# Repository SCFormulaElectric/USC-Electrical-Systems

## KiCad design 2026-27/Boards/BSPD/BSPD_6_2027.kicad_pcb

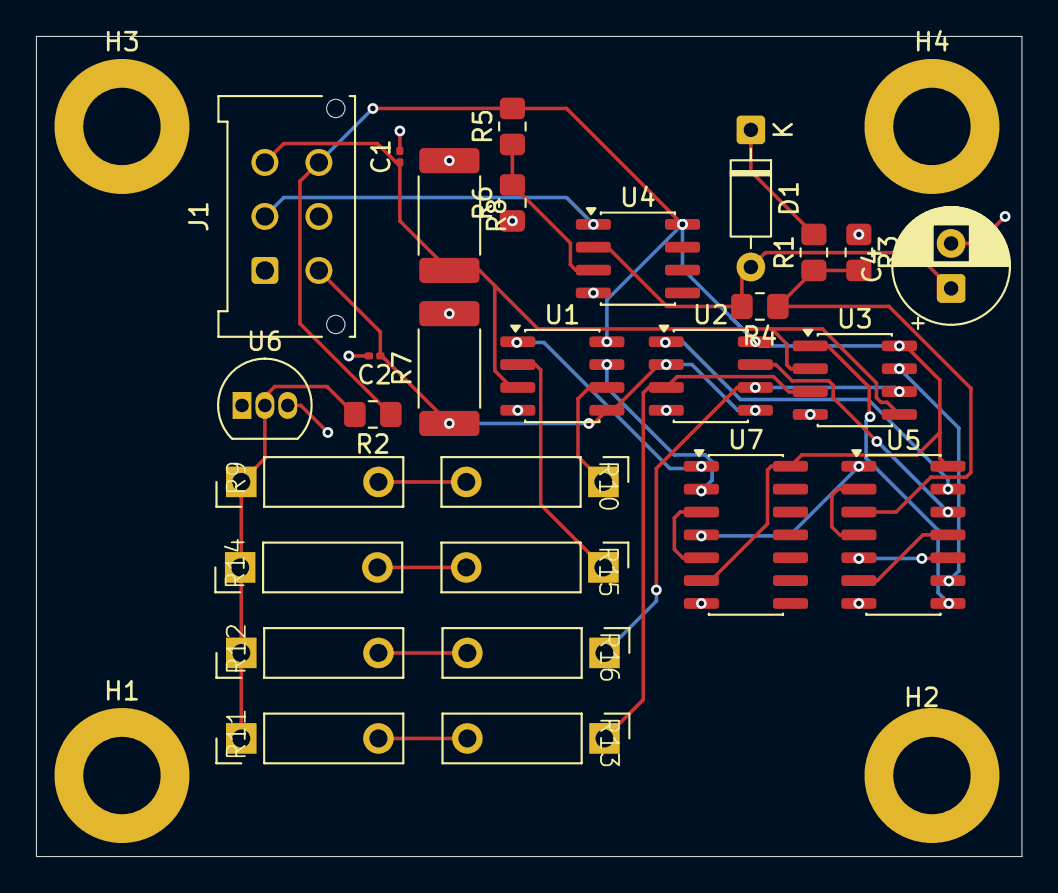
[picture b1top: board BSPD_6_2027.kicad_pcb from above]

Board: 2 copper layers, 54.8 x 45.6 mm, 32 parts (0 on the bottom side), 25 nets.

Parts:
C1, C2: 0.1u; C_0201_0603Metric
C4: 12u; CP_Radial_D6.3mm_P2.50mm
D1: 1N4148; D_DO-35_SOD27_P7.62mm_Horizontal
H1, H2, H3, H4: MountingHole_Pad; MountingHole_4.3mm_M4_DIN965_Pad
J1: 043045-0612; Molex_Micro-Fit_3.0_43045-0612_2x03_P3.00mm_Vertical
R1: 1k; R_0805_2012Metric_Pad1.20x1.40mm_HandSolder
R2: 2.7k; R_0805_2012Metric_Pad1.20x1.40mm_HandSolder
R3: 5k; R_0805_2012Metric_Pad1.20x1.40mm_HandSolder
R4: 50k; R_0805_2012Metric_Pad1.20x1.40mm_HandSolder
R5, R6: 47k; R_0805_2012Metric_Pad1.20x1.40mm_HandSolder
R7, R8: 10k; R_2512_6332Metric_Pad1.40x3.35mm_HandSolder
R9, R11: 1k; SMD TH Adapter
R10, R13: 18k; SMD TH Adapter
R12: 2k; SMD TH Adapter
R14: 1.2k; SMD TH Adapter
R15: 1.3k; SMD TH Adapter
R16: 100; SMD TH Adapter
U1, U2, U3, U4: LM358; SOIC-8_3.9x4.9mm_P1.27mm
U5: HEF4071B (OR); SOIC-14_3.9x8.7mm_P1.27mm
U6: LM4040LP-5; TO-92_Inline
U7: HEF4011B (NAND); SOIC-14_3.9x8.7mm_P1.27mm

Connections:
0.25V: R13.1, U2.3 (+), U3.3 (+)
4.7V: R16.1, U2.6 (-), U3.6 (-)
5V: R2.2, R9.1, R11.1, R12.1, R14.1, U6.2 (K)
12V: J1.6, R2.1, R5.2, U1.8 (V+), U2.8 (V+), U3.8 (V+), U4.8 (V+), U5.14 (VDD), U7.6 (2B), U7.14 (VDD)
BSPD_signal: J1.2, U4.1
GND: C1.2, C2.2, C4.2, H1.1 (1_1), H2.1 (1_1), H3.1 (1_1), H4.1 (1_1), J1.5, R3.1, R6.1, R7.2, R8.1, U1.4 (V-), U2.4 (V-), U3.4 (V-), U4.4 (V-), U5.7 (VSS), U6.3 (A), U7.7 (VSS)
unnamed: C4.1, D1.2 (A), R4.2, U4.2 (-)
unnamed: D1.1 (K), R1.2
unnamed: R15.1, U1.2 (-)
unnamed: R10.1, U1.6 (-)
unnamed: R5.1, R6.2, U4.3 (+)
unnamed: U5.2 (1B), U5.4 (2Y)
unnamed: U5.5 (2A), U5.10 (3Y)
unnamed: U5.6 (2B), U5.11 (4Y)
unnamed: U7.3 (1Y), U7.5 (2A)
brake: C2.1, J1.4, R7.1, U1.5 (+), U2.2 (-), U2.5 (+)
brake_short_ground: U2.1, U5.13 (4B)
brake_short_power: U2.7, U5.12 (4A)
current: C1.1, J1.3, R8.2, U1.3 (+), U3.2 (-), U3.5 (+)
current_short_ground: U3.1, U5.8 (3A)
current_short_power: U3.7, U5.9 (3B)
fault: R1.1, R3.2, R4.1, U5.3 (1Y)
fault_1: U5.1 (1A), U7.4 (2Y)
hard_brake: U1.7, U7.2 (1B)
high_current: U1.1, U7.1 (1A)

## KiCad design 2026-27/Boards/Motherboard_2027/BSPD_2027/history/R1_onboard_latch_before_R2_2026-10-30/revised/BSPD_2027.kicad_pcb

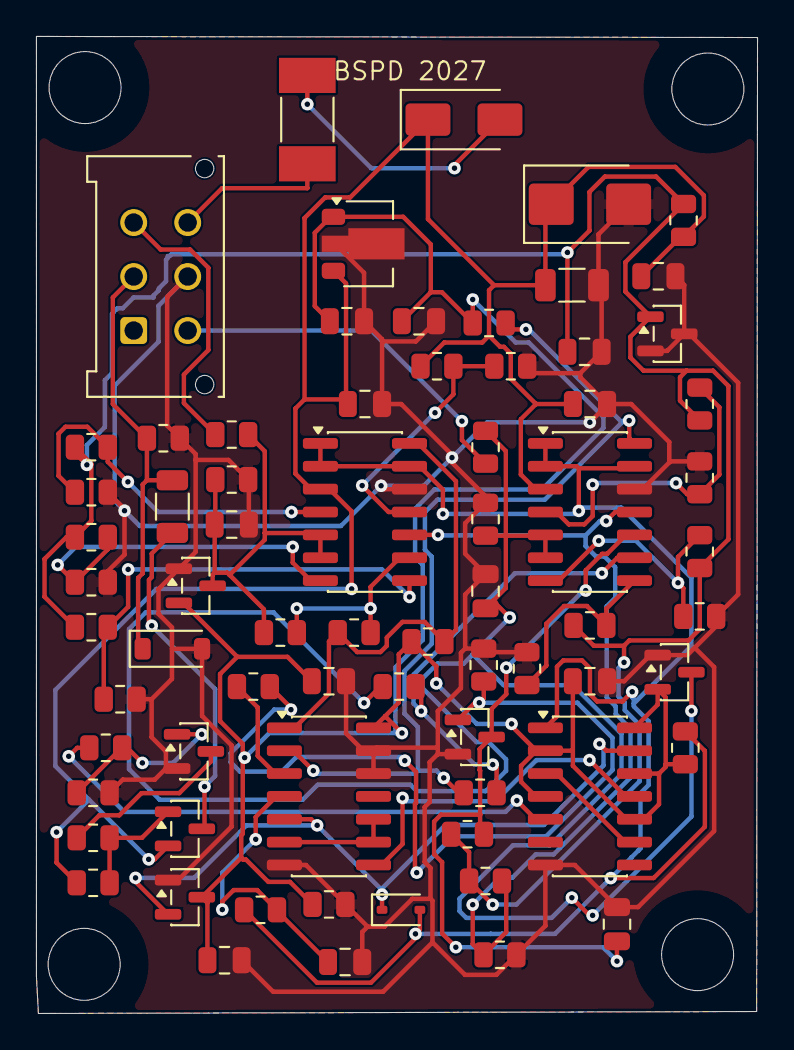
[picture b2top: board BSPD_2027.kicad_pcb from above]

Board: 2 copper layers, 40.1 x 54.3 mm, 71 parts (0 on the bottom side), 37 nets.

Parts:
C1: 10uF/50V; C_1206_3216Metric
C2, C4, C5, C6, C7, C9, C11, C13, C14: 100nF/50V; C_0805_2012Metric
C3: 1uF/50V; C_0805_2012Metric
C8, C10: 10nF/50V; C_0805_2012Metric
C12: 10uF/25V X7R 10%; C_0805_2012Metric
D1: SS14; D_SMA
D2: SMBJ18A; D_SMB
D3: BAT54WS-7-F; D_SOD-323
D4: BZT52C15-7-F; D_SOD-123
F1: 0451.250MRL; Fuse_Littelfuse-NANO2-451_453
J1: 043045-0612; Molex_Micro-Fit_3.0_43045-0612_2x03_P3.00mm_Vertical
Q1: 2N7002,215; SOT-23
Q2: MMBT3904,215; SOT-23
Q3: MMBT3906,215; SOT-23
R1, R11: 1k 1%; R_0805_2012Metric
R2: 3.3k 1%; R_0805_2012Metric
R3, R4, R6, R7, R10, R15, R16, R17, R23: 10k 0.1%; R_0805_2012Metric
R5: 1M 1%; R_0805_2012Metric
R8: 9.53k 0.1%; R_0805_2012Metric
R9: 28k 0.1%; R_0805_2012Metric
R12: 4.7M 1%; R_0805_2012Metric
R13, R19, R21, R24, R26, R32, R34: 10k 1%; R_0805_2012Metric
R14: 33k 1%; R_0805_2012Metric
R18: 115k 1%; R_0805_2012Metric
R20: 8.66k 1%; R_0805_2012Metric
R22: 40.2k 0.1%; R_0805_2012Metric
R25: 2.2M 1%; R_0805_2012Metric
R27: 39k 1%; R_0805_2012Metric
R28, R29: 47k 0.1%; R_0805_2012Metric
R30: 470 1%; R_0805_2012Metric
R31, R35, R37: 100k 1%; R_0805_2012Metric
R33, R36, R39: 47k 1%; R_0805_2012Metric
R38: 2.2k 1%; R_1206_3216Metric
U1: L78L05ABUTR; SOT-89-3
U2: LM4040AIM3-5.0/NOPB; SOT-23
U3: MCP809T-450I/TT; SOT-23
U4, U6: LM2901BIDR; SOIC-14_3.9x8.7mm_P1.27mm
U5, U7: BAT54S,215; SOT-23
U8: 74HC132D,653; SOIC-14_3.9x8.7mm_P1.27mm
U9: 74HC74D,653; SOIC-14_3.9x8.7mm_P1.27mm

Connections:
ARM_CLK: U9.3 (CLK1), U9.9 (Q2)
BOOT_CLK: U8.8 (3Y), U9.11 (CLK2)
BSPD_SIGNAL: D4.1 (K), J1.2, R38.2, R39.1
B_CMP: R24.2, R25.2, U6.9 (IN3+)
B_HARD: R25.1, R26.2, U6.14 (OUT3), U8.2 (1B)
B_HIGH: R20.2, R21.1, U6.7 (IN2+)
B_LOW: R18.2, R19.1, U6.4 (IN1-)
B_RAW: J1.4, R16.1
B_SENSE: C10.1, R16.2, R17.1, R24.1, U6.5 (IN1+), U6.6 (IN2-), U7.3 (K1/A2)
B_THRESH: R22.2, R23.1, U6.8 (IN3-)
CLK_INV: U8.6 (2Y), U8.9 (3A), U8.10 (3B)
C_HIGH: R12.1, R13.2, U4.14 (OUT3), U8.1 (1A)
DISCHARGE: R30.1, U8.3 (1Y)
DIS_GATE: Q1.1 (G), R30.2, R31.1
FAULT_OK: D3.2 (A), R32.2, R33.1, U4.1 (OUT1), U4.2 (OUT2), U4.13 (OUT4), U6.1 (OUT1), U6.2 (OUT2), U6.13 (OUT4), U9.1 (CLR1_N)
GND: C1.2, C2.2, C3.2, C4.2, C5.2, C6.2, C7.2, C8.2, C9.2, C10.2, C11.2, C12.2, C13.2, C14.2, D2.2 (A), D4.2 (A), J1.5, Q1.2 (S), Q2.2 (E), R1.2, R4.2, R6.2, R8.2, R10.2, R15.2, R17.2, R19.2, R21.2, R23.2, R29.2, R31.2, R35.2, R39.2, U1.2 (GND), U2.2 (A), U2.3 (A/NC), U3.1 (GND), U4.12 (GND), U5.1 (A1), U6.12 (GND), U7.1 (A1), U8.7 (GND), U8.12 (4A), U8.13 (4B), U9.7 (GND)
I_CMP: R11.2, R12.2, U4.9 (IN3+)
I_HIGH: R7.2, R8.1, U4.7 (IN2+)
I_LOW: R5.2, R6.1, U4.4 (IN1-)
I_RAW: J1.3, R3.1
I_SENSE: C8.1, R3.2, R4.1, R11.1, U4.5 (IN1+), U4.6 (IN2-), U5.3 (K1/A2)
I_THRESH: R9.2, R10.1, U4.8 (IN3-)
N_BASE: Q2.1 (B), R34.2, R35.1
N_COL: Q2.3 (C), R36.1
OUT_SRC: Q3.3 (C), R38.1
PERMIT: R34.1, U9.5 (Q1)
POR_N: D3.1 (K), U3.2 (RESET_N), U8.5 (2B), U9.13 (CLR2_N)
P_BASE: Q3.1 (B), R36.2, R37.2
REF5: C5.1, R2.2, R5.1, R7.1, R9.1, R18.1, R20.1, R22.1, R27.1, R28.1, U2.1 (K)
REF_HALF: R28.2, R29.1, U4.10 (IN4-), U6.11 (IN4+)
START_RC: C14.1, R33.2, U8.4 (2A)
TIMER: C12.1, Q1.3 (D), R27.2, U6.10 (IN4-)
V5: C3.1, C4.1, C6.1, C11.1, C13.1, R1.1, R13.1, R26.1, R32.1, U1.1 (OUT), U3.3 (VDD), U5.2 (K2), U7.2 (K2), U8.14 (VCC), U9.2 (D1), U9.4 (PRE1_N), U9.10 (PRE2_N), U9.12 (D2), U9.14 (VCC)
VIN: F1.1, J1.6
VIN_DIV: R14.2, R15.1, U4.11 (IN4+)
VIN_F: D1.2 (A), F1.2
VP: C1.1, C2.1, C7.1, C9.1, D1.1 (K), D2.1 (K), Q3.2 (E), R2.1, R14.1, R37.1, U1.3 (IN), U4.3 (VCC), U6.3 (VCC)

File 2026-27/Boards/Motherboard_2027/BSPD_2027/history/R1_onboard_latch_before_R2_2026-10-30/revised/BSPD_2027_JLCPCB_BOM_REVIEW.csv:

Comment,Designator,Footprint,LCSC Part #
043045-0612,J1,Molex_Micro-Fit_3.0_43045-0612_2x03_P3.00mm_Vertical,C234188
0451.250MRL,F1,Fuse_Littelfuse-NANO2-451_453,C151116
SS14,D1,D_SMA,C2480
SMBJ18A,D2,D_SMB,C151256
10uF/50V,C1,C_1206_3216Metric,C77092
100nF/50V,"C2,C4,C5,C6,C7,C9,C11,C13,C14",C_0805_2012Metric,C1711
L78L05ABUTR,U1,SOT-89-3,C42738
1uF/50V,C3,C_0805_2012Metric,C28323
1k 1%,"R1,R11",R_0805_2012Metric,C17513
3.3k 1%,R2,R_0805_2012Metric,C26010
LM4040AIM3-5.0/NOPB,U2,SOT-23,C140239
MCP809T-450I/TT,U3,SOT-23,C511285
LM2901BIDR,"U4,U6",SOIC-14_3.9x8.7mm_P1.27mm,C22427890
10k 0.1%,"R3,R4,R6,R7,R10,R15,R16,R17,R23",R_0805_2012Metric,C110775
10nF/50V,"C8,C10",C_0805_2012Metric,C282728
"BAT54S,215","U5,U7",SOT-23,C47546
1M 1%,R5,R_0805_2012Metric,C17514
9.53k 0.1%,R8,R_0805_2012Metric,C865722
28k 0.1%,R9,R_0805_2012Metric,C865356
4.7M 1%,R12,R_0805_2012Metric,C17674
10k 1%,"R13,R19,R21,R24,R26,R32,R34",R_0805_2012Metric,C17414
33k 1%,R14,R_0805_2012Metric,C17633
115k 1%,R18,R_0805_2012Metric,C407430
8.66k 1%,R20,R_0805_2012Metric,C17832
40.2k 0.1%,R22,R_0805_2012Metric,C865475
2.2M 1%,R25,R_0805_2012Metric,C137552
"74HC132D,653",U8,SOIC-14_3.9x8.7mm_P1.27mm,C5601
39k 1%,R27,R_0805_2012Metric,C25826
10uF/25V X7R 10%,C12,C_0805_2012Metric,C237493
47k 0.1%,"R28,R29",R_0805_2012Metric,C865515
470 1%,R30,R_0805_2012Metric,C17710
100k 1%,"R31,R35,R37",R_0805_2012Metric,C149504
"2N7002,215",Q1,SOT-23,C65189
"74HC74D,653",U9,SOIC-14_3.9x8.7mm_P1.27mm,C27597
BAT54WS-7-F,D3,D_SOD-323,C124205
47k 1%,"R33,R36,R39",R_0805_2012Metric,C17713
"MMBT3904,215",Q2,SOT-23,C426835
"MMBT3906,215",Q3,SOT-23,C75549
2.2k 1%,R38,R_1206_3216Metric,C17948
BZT52C15-7-F,D4,D_SOD-123,C177014

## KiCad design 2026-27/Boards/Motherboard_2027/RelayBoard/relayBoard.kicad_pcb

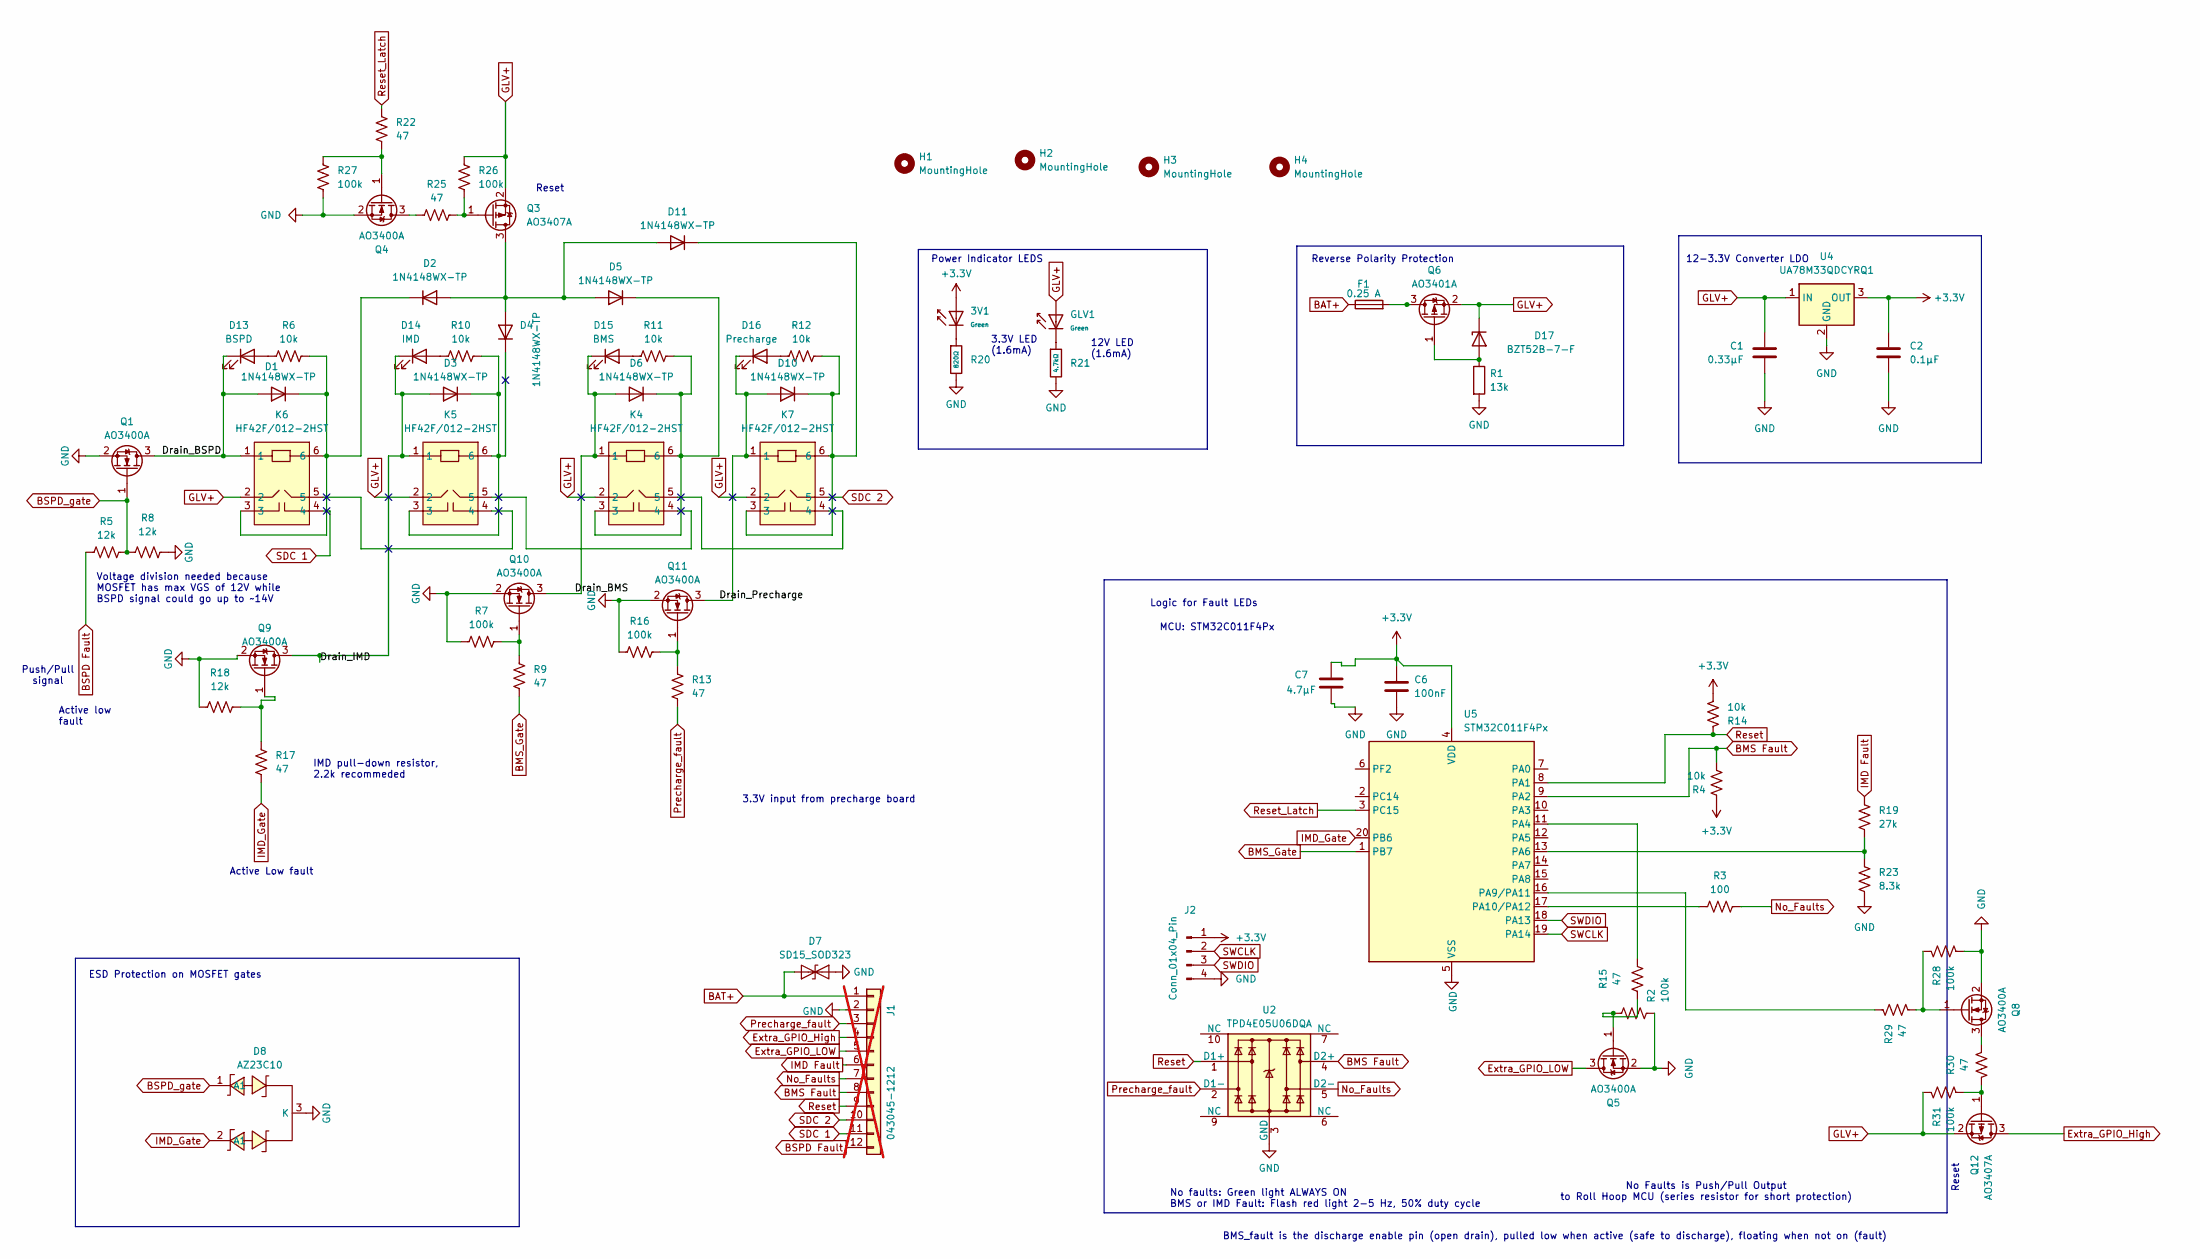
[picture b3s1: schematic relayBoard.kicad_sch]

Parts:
3V1: Green; LED_0805_2012Metric; Forward Voltage (VF) 1.6V~2.6V; Part NCD0805R1; LCSC C84256
C1: 0.33μF; C_0402_1005Metric
C2: 0.1μF; C_0402_1005Metric
C6: 100nF; C_0402_1005Metric
C7: 4.7μF; C_0402_1005Metric
D1, D2, D3, D4, D5, D6, D10, D11: 1N4148WX-TP; D_SOD-323
D7: SD15_SOD323; D_SOD-323
D8: AZ23C10; SOT-23; LCSC Part C32677
D13: BSPD; LED_0805_2012Metric
D14: IMD; LED_0805_2012Metric
D15: BMS; LED_0805_2012Metric
D16: Precharge; LED_0805_2012Metric
D17: BZT52B-7-F; D_SOD-323
F1: 0.25 A; Fuse_1206_3216Metric_Pad1.42x1.75mm_HandSolder
GLV1: Green; LED_0805_2012Metric; Forward Voltage (VF) 1.6V~2.6V; Part NCD0805R1; LCSC C84260
H1, H2, H3, H4: MountingHole; MountingHole_4.3mm_M4
J1: 043045-1212; Molex_Micro-Fit_3.0_43045-1200_2x06_P3.00mm_Horizontal; not fitted
J2: Conn_01x04_Pin; PinHeader_1x04_P2.54mm_Vertical
K4, K5, K6, K7: HF42F/012-2HST; RELAYS-TH_HF42F-XX-2HSX-XXX; LCSC Part C165254
Q1, Q4, Q5, Q8, Q9, Q10, Q11: AO3400A; SOT-23
Q3, Q12: AO3407A; SOT-23
Q6: AO3401A; SOT-23
R1: 13k; R_0603_1608Metric
R2, R7, R16, R26, R27, R28, R31: 100k; R_0603_1608Metric
R3: 100; R_0603_1608Metric
R4, R6, R10, R11, R12, R14: 10k; R_0603_1608Metric
R5, R8, R18: 12k; R_0603_1608Metric
R9, R13, R15, R17, R22, R25, R29, R30: 47; R_0603_1608Metric
R19: 27k; R_0603_1608Metric
R20: 820Ω; R_0603_1608Metric; Overload Voltage (Max) 75V; Tolerance ±1%; Part 0603WAF8200T5E; LCSC C23253
R21: 4.7kΩ; R_0603_1608Metric; Overload Voltage (Max) 75V; Tolerance ±1%; Part 0603WAF8200T5E; LCSC C23253
R23: 8.3k; R_0603_1608Metric
U2: TPD4E05U06DQA; USON-10_2.5x1.0mm_P0.5mm
U4: UA78M33QDCYRQ1; TO-252-2
U5: STM32C011F4Px; TSSOP-20_4.4x6.5mm_P0.65mm

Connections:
+3.3V: 3V1.2, C2.1, C6.2, C7.1, J2.1, R4.2, R14.2, U4.3 (OUT), U5.4 (VDD)
/Drain_BMS: D6.2 (A), D15.1 (K), K4.1, Q10.3 (D)
/Drain_BSPD: D1.2 (A), D13.1 (K), K6.1, Q1.3 (D)
/Drain_IMD: D3.2 (A), D14.1 (K), K5.1, Q9.3 (D)
/Drain_Precharge: D10.2 (A), D16.1 (K), K7.1, Q11.3 (D)
BAT+: D7.1 (A1), F1.1, J1.1
BMS Fault: J1.8, R4.1, U2.4 (D2+), U5.9 (PA2)
BMS_Gate: R9.2, U5.1 (PB7)
BSPD Fault: J1.12, R5.2
BSPD_gate: D8.1 (A1), Q1.1 (G), R5.1, R8.2
Extra_GPIO_High: J1.4, Q12.3 (D)
Extra_GPIO_LOW: J1.5, Q5.3 (D)
GLV+: C1.1, D17.1 (K), GLV1.2, K4.2, K5.2, K6.2, K7.2, Q3.2 (S), Q6.2 (S), Q12.2 (S), R26.2, R31.2, U4.1 (IN)
GND: C1.2, C2.2, C6.1, C7.2, D7.2 (A2), D8.3 (K), J1.2, J2.4, Q1.2 (S), Q4.2 (S), Q5.2 (S), Q8.2 (S), Q9.2 (S), Q10.2 (S), Q11.2 (S), R1.2, R2.1, R7.1, R8.1, R16.1, R18.1, R20.2, R21.2, R23.2, R27.1, R28.1, U2.3 (GND), U2.8 (GND), U4.2 (GND), U5.5 (VSS)
IMD Fault: J1.6, R19.1
IMD_Gate: D8.2 (A1), R17.2, U5.20 (PB6)
unnamed: 3V1.1, R20.1
unnamed: D1.1 (K), D2.1 (K), K6.3, K6.6, R6.2
unnamed: D3.1 (K), D4.1 (K), K5.3, K5.6, R10.2
unnamed: D5.1 (K), D6.1 (K), K4.3, K4.6, R11.2
unnamed: D10.1 (K), D11.1 (K), K7.3, K7.6, R12.2
unnamed: D2.2 (A), D4.2 (A), D5.2 (A), D11.2 (A), Q3.3 (D)
unnamed: D13.2 (A), R6.1
unnamed: D14.2 (A), R10.1
unnamed: D15.2 (A), R11.1
unnamed: D16.2 (A), R12.1
unnamed: D17.2 (A), Q6.1 (G), R1.1
unnamed: GLV1.1, R21.1
unnamed: K4.4, K5.5
unnamed: K4.5, K7.4
unnamed: K5.4, K6.5
unnamed: Q3.1 (G), R25.2, R26.1
unnamed: Q4.3 (D), R25.1
unnamed: Q4.1 (G), R22.2, R27.2
unnamed: Q5.1 (G), R2.2, R15.2
unnamed: F1.2, Q6.3 (D)
unnamed: Q8.3 (D), R30.1
unnamed: Q8.1 (G), R28.2, R29.2
unnamed: Q9.1 (G), R17.1, R18.2
unnamed: Q10.1 (G), R7.2, R9.1
unnamed: Q11.1 (G), R13.1, R16.2
unnamed: Q12.1 (G), R30.2, R31.1
unnamed: R15.1, U5.11 (PA4)
unnamed: R19.2, R23.1, U5.13 (PA6)
unnamed: R29.1, U5.16 (PA9/PA11)
unnamed: R3.1, U5.17 (PA10/PA12)
No_Faults: J1.7, R3.2, U2.5 (D2-)
Precharge_fault: J1.3, R13.2, U2.2 (D1-)
Reset: J1.9, R14.1, U2.1 (D1+), U5.8 (PA1)
Reset_Latch: R22.1, U5.3 (PC15)
SDC 1: J1.11, K6.4
SDC 2: J1.10, K7.5
SWCLK: J2.2, U5.19 (PA14)
SWDIO: J2.3, U5.18 (PA13)

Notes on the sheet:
Active low fault
12V LED (1.6mA)
Reset
MCU: STM32C011F4Px
12-3.3V Converter LDO
ESD Protection on MOSFET gates
IMD pull-down resistor, 2.2k recommeded
Logic for Fault LEDs
Push/Pull signal
No Faults is Push/Pull Output to Roll Hoop MCU (series resistor for short protection)
3.3V input from precharge board
3.3V LED (1.6mA)
BMS_fault is the discharge enable pin (open drain), pulled low when active (safe to discharge), floating when not on (fault)
Reverse Polarity Protection
Active Low fault
Power Indicator LEDS
Voltage division needed because MOSFET has max VGS of 12V while BSPD signal could go up to ~14V
No faults: Green light ALWAYS ON BMS or IMD Fault: Flash red light 2-5 Hz, 50% duty cycle

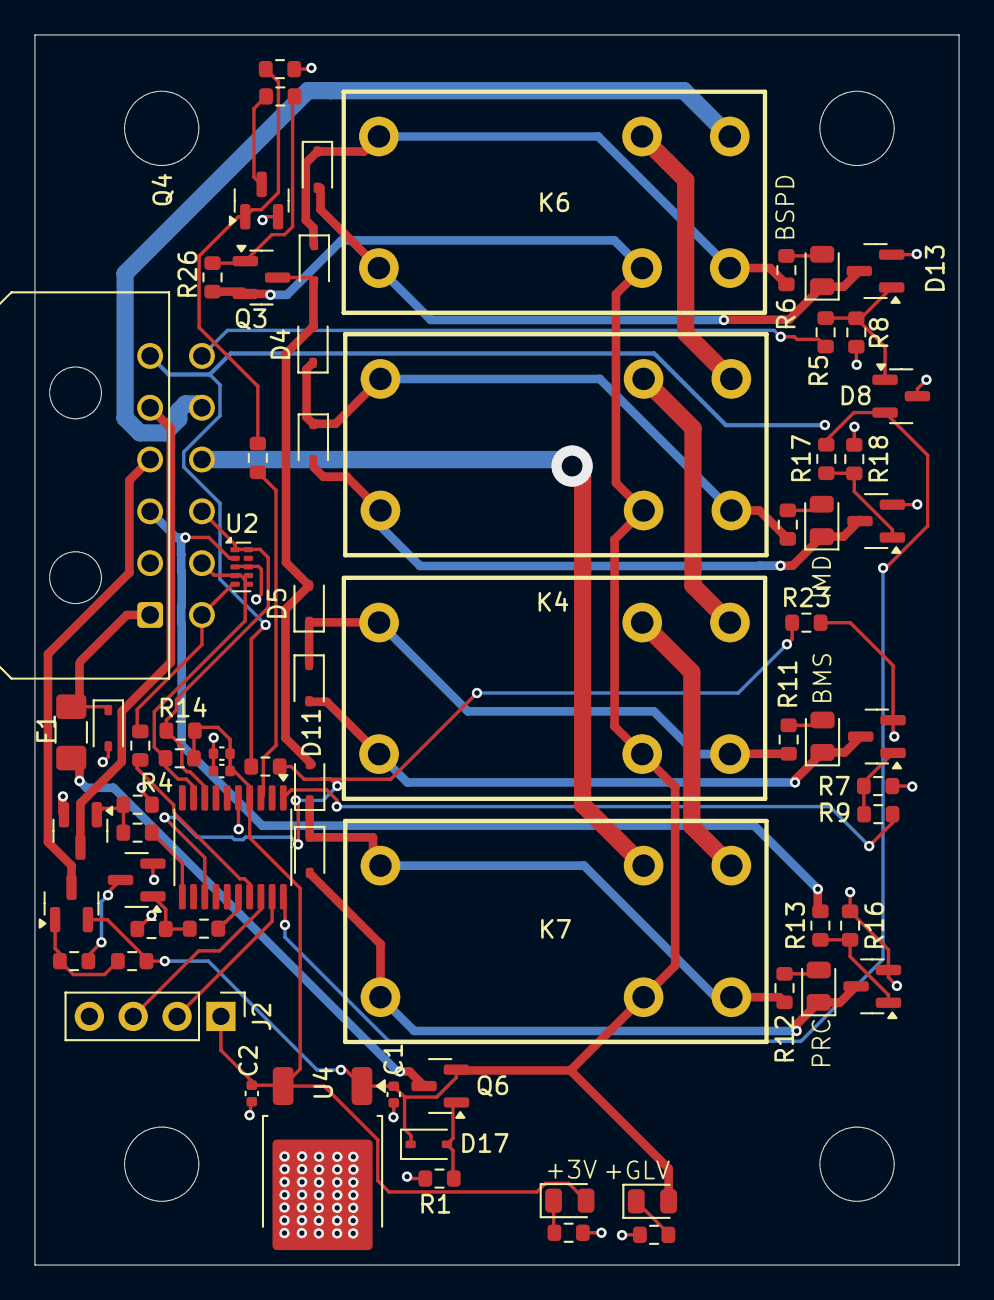
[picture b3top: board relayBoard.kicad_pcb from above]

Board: 2 copper layers, 53.5 x 71.2 mm, 75 parts (0 on the bottom side), 54 nets.

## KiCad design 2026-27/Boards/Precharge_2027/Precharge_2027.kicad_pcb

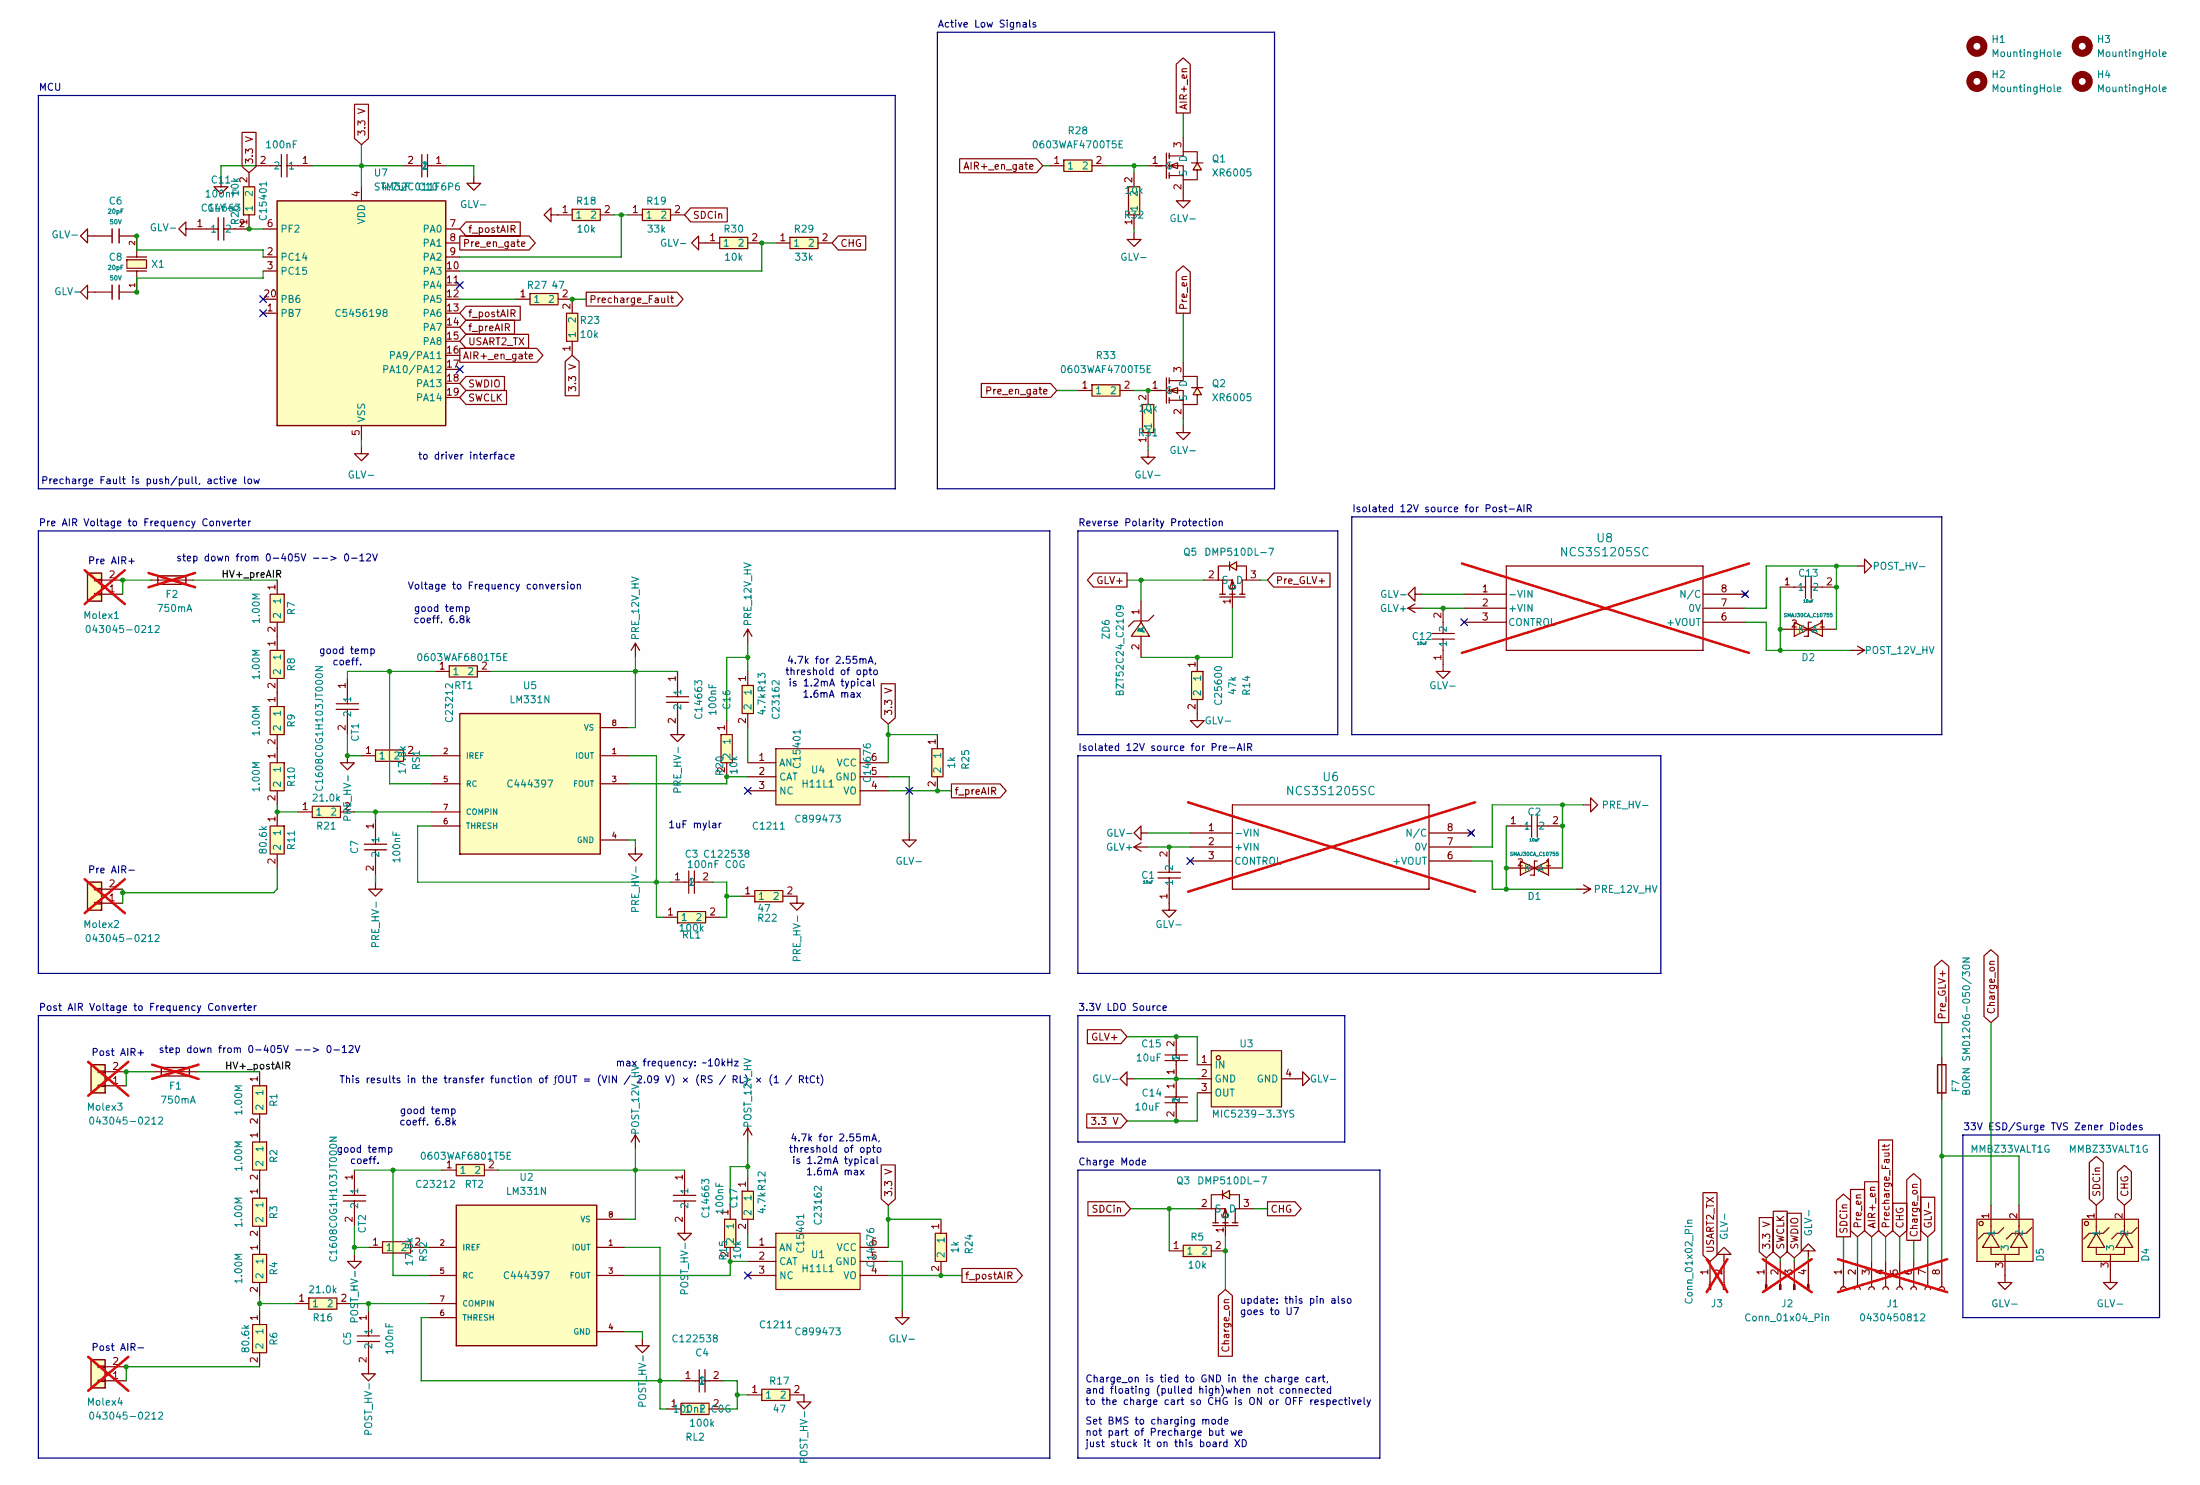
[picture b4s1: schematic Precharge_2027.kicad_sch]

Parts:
C1, C2, C12, C13: 10uF; C0805; MPN GRM21BR61H106KE43L; LCSC Part C440198
C3, C4: 100nF C0G; C1206; MPN CC1206JKNPO9BN104; LCSC Part C577121
C5, C7, C9, C11, C16, C17: 100nF; C0603; LCSC Part C14663
C6, C8: 20pF; C_0603_1608Metric; Voltage Rated 50V; Tolerance ±5%; Part CL10C200JB8NNNC; LCSC C1648
C10: 4.7uF; C0603; LCSC Part C69335
C14, C15: 10uF; C1206; LCSC Part C13585
CT1, CT2: C1608C0G1H103JT000N; C0603; LCSC Part C76599
D1, D2: SMAJ30CA_C10755; SMA_L4.4-W2.6-LS5.0-BI; MPN SMAJ30CA; LCSC Part C10755
D4, D5: MMBZ33VALT1G; SOT-23-3_L2.9-W1.3-P1.90-LS2.4-BR; MPN MMBZ33VALT1G; LCSC Part C185935
F1, F2: 750mA; FUSE_BK_PCS; not fitted
F7: BORN SMD1206-050/30N; Fuse_1206_3216Metric_Pad1.42x1.75mm_HandSolder; JLCPCB Part Number C6165188
H1, H2, H3, H4: MountingHole; MountingHole_4.3mm_M4
J1: 0430450812; Molex_Micro-Fit_3.0_43045-0812_2x04_P3.00mm_Vertical; not fitted
J2: Conn_01x04_Pin; PinHeader_1x04_P2.54mm_Vertical; not fitted
J3: Conn_01x02_Pin; PinHeader_1x02_P2.54mm_Vertical; not fitted
Molex1, Molex2, Molex3, Molex4: 043045-0212; CONN-TH_430450212; not fitted
Q1, Q2: XR6005; SOT-23-3_L2.9-W1.3-P0.95-LS2.4-BR; MPN XR6005; LCSC Part C42456827
Q3, Q5: DMP510DL-7; SOT-23-3_L2.9-W1.3-P1.90-LS2.4-BR; MPN DMP510DL-7; LCSC Part C397953
R1, R2, R3, R4, R7, R8, R9, R10: 1.00M; R1206; MPN RT1206BRD071ML; LCSC Part C309662
R5, R15, R20, R23, R26, R31, R32: 10k; R0603; LCSC Part C15401
R6, R11: 80.6k; R0603; MPN RT0603BRD0780K6L; LCSC Part C861568
R12, R13: 4.7k; R0603; LCSC Part C23162
R14: 47k; R0603; LCSC Part C25600
R16, R21: 21.0k; R0603; MPN RT0603BRD0721KL; LCSC Part C861228
R17, R22, R27: 47; R0603; LCSC Part C1211
R18, R30: 10k; R0805; MPN 0805W8F1002T5E; LCSC Part C17414
R19, R29: 33k; R0805; MPN 0805W8F3302T5E; LCSC Part C17633
R24, R25: 1k; R0603; LCSC Part C14676
R28, R33: 0603WAF4700T5E; R0603; MPN 0603WAF4700T5E; LCSC Part C23179
RL1, RL2: 100k; R0603; MPN RT0603BRD07100KL; LCSC Part C122538
RS1, RS2: 17.8k; R0603; MPN RT0603BRD0717K8L; LCSC Part C705729
RT1, RT2: 0603WAF6801T5E; R0603; LCSC Part C23212
U1, U4: H11L1; SOP-6_L8.5-W6.4-P2.54-LS9.2-BL; LCSC Part C899473
U2, U5: LM331N; DIP-8_L9.8-W6.6-P2.54-LS7.6-BL; PARTREV C; LCSC Part C444397
U3: MIC5239-3.3YS; SOT-223-3_L6.7-W3.7-P2.30-LS7.0-BR; MPN MIC5239-3.3YS; LCSC Part C638649
U6, U8: NCS3S1205SC; NCS3S1205SC_MUR; not fitted
U7: STM32C011F6P6; TSSOP-20_4.4x6.5mm_P0.65mm; LCSC Part C5456198
X1: X50328MSB2GI; OSCCC500X320X135; Frequency Tolerance ±10ppm; Part X50328MSB2GI; LCSC C115962
ZD6: BZT52C24_C2109; SOD-123_L2.8-W1.8-LS3.7-RD; MPN BZT52C24; LCSC Part C2109

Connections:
3.3 V: C9.1, C10.2, C14.2, J2.1, R23.1, R24.1, R25.1, R26.2, U1.6 (VCC), U3.3 (OUT), U4.6 (VCC), U7.4 (VDD)
/HV+_postAIR: F1.1, R1.1
/HV+_preAIR: F2.1, R7.1
AIR+_en: J1.3, Q1.3 (D)
AIR+_en_gate: R28.1, U7.16 (PA9/PA11)
CHG: D4.2, J1.5, Q3.3 (D), R29.2
Charge_on: D5.1, J1.6, Q3.1 (G), R5.2
GLV+: C1.2, C12.2, C15.2, Q5.2 (S), U3.1 (IN), U6.2 (+VIN), U8.2 (+VIN), ZD6.1 (K)
GLV-: C1.1, C6.1, C8.1, C9.2, C10.1, C11.1, C12.1, C14.1, C15.1, D4.3, D5.3, J1.7, J2.4, J3.2, Q1.2 (S), Q2.2 (S), R14.2, R18.1, R30.1, R31.1, R32.1, U1.5 (GND), U3.2 (GND), U3.4 (GND), U4.5 (GND), U6.1 (-VIN), U7.5 (VSS), U8.1 (-VIN)
unnamed: C3.2, R22.1, RL1.2
unnamed: C4.2, R17.1, RL2.2
unnamed: D5.2, F7.2, J1.8
unnamed: F2.2, Molex1.1, Molex1.2
unnamed: F1.2, Molex3.1, Molex3.2
unnamed: Q1.1 (G), R28.2, R32.2
unnamed: Q2.1 (G), R31.2, R33.2
unnamed: Q5.1 (G), R14.1, ZD6.2 (A)
unnamed: R1.2, R2.1
unnamed: R2.2, R3.1
unnamed: R3.2, R4.1
unnamed: R7.2, R8.1
unnamed: R8.2, R9.1
unnamed: R9.2, R10.1
unnamed: R10.2, R11.1, R21.1
unnamed: R4.2, R6.1, R16.1
unnamed: R12.2, U1.1 (AN)
unnamed: R15.2, U1.2 (CAT), U2.3 (FOUT)
unnamed: C5.1, R16.2, U2.7 (COMPIN)
unnamed: C4.1, RL2.1, U2.1 (IOUT), U2.6 (THRESH)
unnamed: RS2.2, U2.2 (IREF)
unnamed: CT2.1, RT2.1, U2.5 (RC)
unnamed: R13.2, U4.1 (AN)
unnamed: R20.2, U4.2 (CAT), U5.3 (FOUT)
unnamed: C7.1, R21.2, U5.7 (COMPIN)
unnamed: C3.1, RL1.1, U5.1 (IOUT), U5.6 (THRESH)
unnamed: RS1.2, U5.2 (IREF)
unnamed: CT1.1, RT1.1, U5.5 (RC)
unnamed: R18.2, R19.1, U7.9 (PA2)
unnamed: R29.1, R30.2, U7.10 (PA3)
unnamed: R27.1, U7.12 (PA5)
unnamed: C6.2, U7.2 (PC14), X1.2
unnamed: C8.2, U7.3 (PC15), X1.1
unnamed: C11.2, R26.1, U7.6 (PF2)
POST_12V_HV: C13.1, C17.1, D2.2 (A), R12.1, R15.1, RT2.2, U2.8 (VS), U8.6 (+VOUT)
PRE_12V_HV: C2.1, C16.1, D1.2 (A), R13.1, R20.1, RT1.2, U5.8 (VS), U6.6 (+VOUT)
Pre_GLV+: F7.1, Q5.3 (D)
Pre_en: J1.2, Q2.3 (D)
Pre_en_gate: R33.1, U7.8 (PA1)
Precharge_Fault: J1.4, R23.2, R27.2
SDCin: D4.1, J1.1, Q3.2 (S), R5.1, R19.2
SWCLK: J2.2, U7.19 (PA14)
SWDIO: J2.3, U7.18 (PA13)
USART2_TX: J3.1, U7.15 (PA8)
f_postAIR: R24.2, U1.4 (VO), U7.7 (PA0), U7.13 (PA6)
f_preAIR: R25.2, U4.4 (VO), U7.14 (PA7)

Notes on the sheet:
Active Low Signals
update: this pin also goes to U7
33V ESD/Surge TVS Zener Diodes
Charge Mode
4.7k for 2.55mA, threshold of opto is 1.2mA typical 1.6mA max
MCU
step down from 0-405V --> 0-12V
Isolated 12V source for Post-AIR
Reverse Polarity Protection
good temp coeff. 6.8k
Charge_on is tied to GND in the charge cart, and floating (pulled high)when not connected to the charge cart so CHG is ON or OFF respectively
Post AIR-
max frequency: ~10kHz
Pre AIR Voltage to Frequency Converter
Post AIR+
Isolated 12V source for Pre-AIR
Post AIR Voltage to Frequency Converter
1uF mylar
Set BMS to charging mode not part of Precharge but we just stuck it on this board XD
This results in the transfer function of ƒOUT = (VIN / 2.09 V) × (RS / RL) × (1 / RtCt)
3.3V LDO Source
good temp coeff.
Pre AIR-
Voltage to Frequency conversion
to driver interface
Precharge Fault is push/pull, active low
Pre AIR+

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
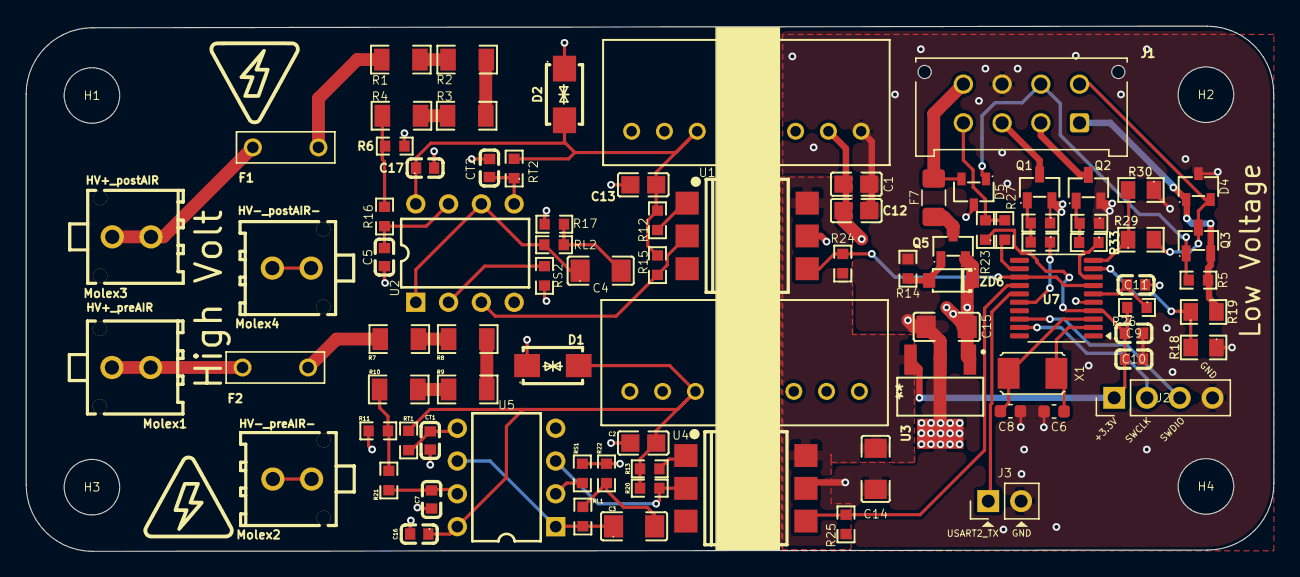
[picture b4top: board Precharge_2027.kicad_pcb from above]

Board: 4 copper layers, 96.6 x 40.7 mm, 90 parts (0 on the bottom side), 57 nets.
